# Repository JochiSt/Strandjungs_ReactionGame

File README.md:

# Reaction Game

The idea of this game is that you press a button and after some time (random)
one or two (selectable) wooden rods are dropped. The player has to catch these 
falling rods.

## Modes

There are four different modes implemented. The selection of the modes is done 
via the binary encoded input from the switch (marked with Drop 1/2).
Switch 1 is the LSB and two the MSB.

| Switch 2 	| Switch 1 	| Mode 	| Action                                                                   	|
|----------	|----------	|------	|--------------------------------------------------------------------------	|
| 0        	| 0        	| 0    	| dropping a single random rod                                             	|
| 0        	| 1        	| 1    	| dropping two random rods at the same time                                	|
| 1        	| 0        	| 2    	| dropping two random rods at different times                              	|
| 1        	| 1        	| 3    	| dropping all rods after each other (with waiting time) in a random order 	|

## Operation Voltage & Current
The operation voltage is 12V and the power consumption is about 1.5A (5x200mA for the magnets). 

## Hardware used
* [ElectroMagnets](https://www.amazon.de/gp/product/B07QNL3CJ2)

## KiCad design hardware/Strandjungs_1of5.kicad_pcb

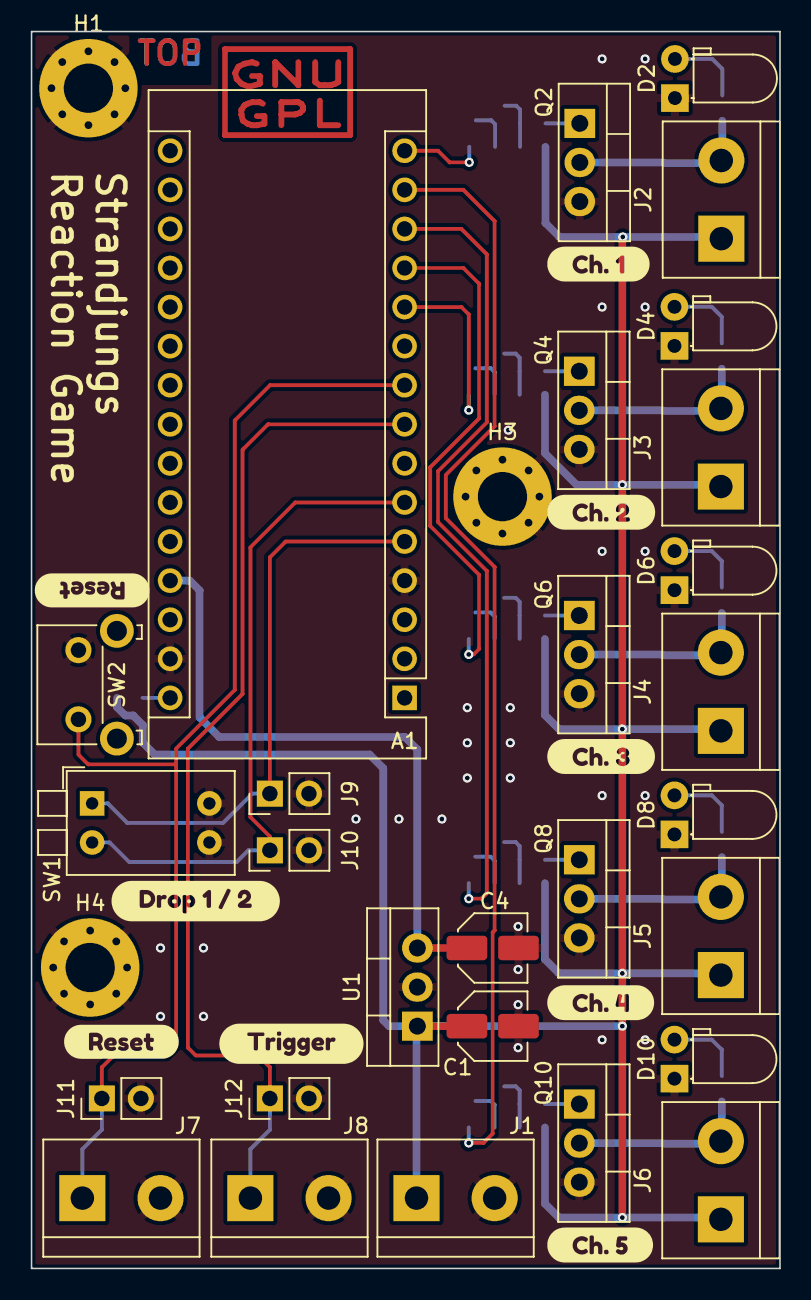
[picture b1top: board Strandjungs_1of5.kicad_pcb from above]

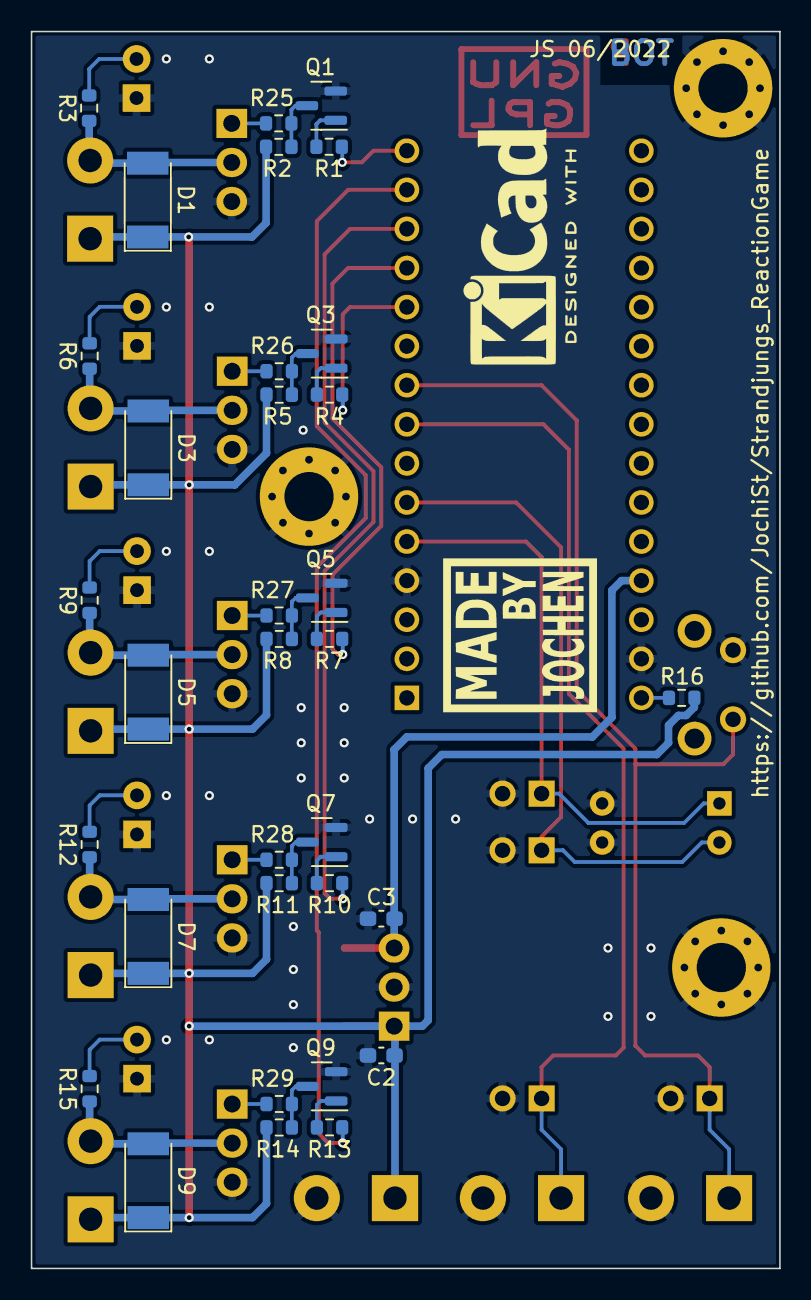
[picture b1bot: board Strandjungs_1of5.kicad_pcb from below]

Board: 2 copper layers, 48.6 x 80.4 mm, 73 parts (33 on the bottom side), 38 nets.

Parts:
A1: Arduino_Nano_v2.x; Arduino_Nano
C1: 1uF; C_Elec_4x5.4
C2, C3: 100n; C_0603_1608Metric_Pad1.08x0.95mm_HandSolder
C4: 10uF; C_Elec_4x5.4
D1, D3, D5, D7, D9: SM4001; D_MELF
D2, D4, D6, D8, D10: LED; LED_D3.0mm_Horizontal_O1.27mm_Z2.0mm
H1, H3, H4: MountingHole_Pad; MountingHole_3.2mm_M3_Pad_Via
J1, J2, J3, J4, J5, J6, J7, J8: Screw_Terminal_01x02; TerminalBlock_bornier-2_P5.08mm
J9, J10, J11, J12: Conn_01x02; PinHeader_1x02_P2.54mm_Vertical
Q1, Q3, Q5, Q7, Q9: BC847; SOT-23
Q2, Q4, Q6, Q8, Q10: BUZ11; TO-220-3_Vertical
R1, R2, R4, R5, R7, R8, R10, R11, R13, R14: 10k; R_0603_1608Metric
R3, R6, R9, R12, R15: 5k6; R_0603_1608Metric
R16: dnp; R_0603_1608Metric
R25, R26, R27, R28, R29: 56; R_0603_1608Metric
SW1: SW_DIP_x02; SW_DIP_SPSTx02_Piano_10.8x6.64mm_W7.62mm_P2.54mm
SW2: SW_Push; SW_Tactile_SKHH_Angled
U1: L7805; TO-220-3_Vertical
kibuzzard-62B9DC86: G***; kibuzzard-62B9DC86
kibuzzard-62B9DCAD, kibuzzard-62B9DCAD#2: G***; kibuzzard-62B9DCAD
kibuzzard-62B9DCC5: G***; kibuzzard-62B9DCC5
kibuzzard-62B9DCD6: G***; kibuzzard-62B9DCD6
kibuzzard-62B9DCE2: G***; kibuzzard-62B9DCE2
kibuzzard-62B9DCF0: G***; kibuzzard-62B9DCF0
kibuzzard-62B9DD05: G***; kibuzzard-62B9DD05
kibuzzard-62B9DD70: G***; kibuzzard-62B9DD70

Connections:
+5V: A1.27 (+5V), C3.1, C4.1, U1.3 (OUT)
+12V: C1.1, C2.1, D1.1 (K), D3.1 (K), D5.1 (K), D7.1 (K), D9.1 (K), J1.1, J2.1, J3.1, J4.1, J5.1, J6.1, R2.1, R5.1, R8.1, R11.1, R14.1, R16.1, U1.1 (IN)
/Channel 0/MAG_RTN: D1.2 (A), J2.2, Q2.2 (D), R3.1
/Channel 1/MAG_RTN: D3.2 (A), J3.2, Q4.2 (D), R6.1
/Channel 2/MAG_RTN: D5.2 (A), J4.2, Q6.2 (D), R9.1
/Channel 3/MAG_RTN: D7.2 (A), J5.2, Q8.2 (D), R12.1
/Channel 4/MAG_RTN: D9.2 (A), J6.2, Q10.2 (D), R15.1
/RESET: A1.9 (D6), J7.1, J11.1, SW2.1
/SEL_0: A1.5 (D2), J9.1, SW1.1
/SEL_1: A1.6 (D3), J10.1, SW1.2
/SWITCH0: A1.15 (D12), R1.1
/SWITCH1: A1.11 (D8), R4.1
/SWITCH2: A1.12 (D9), R7.1
/SWITCH3: A1.13 (D10), R10.1
/SWITCH4: A1.14 (D11), R13.1
/TRIGGER: A1.8 (D5), J8.1, J12.1
GND: A1.4 (GND), A1.29 (GND), C1.2, C2.2, C3.2, C4.2, D2.1 (K), D4.1 (K), D6.1 (K), D8.1 (K), D10.1 (K), H1.1, H3.1, H4.1, J1.2, J7.2, J8.2, J9.2, J10.2, J11.2, J12.2, Q1.2 (E), Q2.3 (S), Q3.2 (E), Q4.3 (S), Q5.2 (E), Q6.3 (S), Q7.2 (E), Q8.3 (S), Q9.2 (E), Q10.3 (S), SW1.3, SW1.4, SW2.2, U1.2 (GND)
unnamed: A1.30 (VIN), R16.2
unnamed: D2.2 (A), R3.2
unnamed: D4.2 (A), R6.2
unnamed: D6.2 (A), R9.2
unnamed: D8.2 (A), R12.2
unnamed: D10.2 (A), R15.2
unnamed: Q1.1 (B), R1.2
unnamed: Q1.3 (C), R2.2, R25.1
unnamed: Q2.1 (G), R25.2
unnamed: Q3.1 (B), R4.2
unnamed: Q3.3 (C), R5.2, R26.1
unnamed: Q4.1 (G), R26.2
unnamed: Q5.1 (B), R7.2
unnamed: Q5.3 (C), R8.2, R27.1
unnamed: Q6.1 (G), R27.2
unnamed: Q7.1 (B), R10.2
unnamed: Q7.3 (C), R11.2, R28.1
unnamed: Q8.1 (G), R28.2
unnamed: Q9.1 (B), R13.2
unnamed: Q9.3 (C), R14.2, R29.1
unnamed: Q10.1 (G), R29.2

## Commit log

2022-06-21 started firmware script
    wrote down the basic ideas and the basic concept.
2022-06-22 added README.md
2022-06-27 added hardware layout
    started layout for driver PCB
2022-06-27 Update .gitignore
    added *.log and *.zip
2022-06-27 first iteration of layout almost done
2022-06-27 added 7805 as voltage regulator
2022-06-28 updated layout
2022-06-28 added description of function
2022-06-28 updated AISLER project ID
2022-06-28 adjusted production output
2022-06-28 added ibom
2022-06-28 ignore PDF
2022-06-29 added pins from schematic
2022-07-03 added rough programming scheme
    some action implemented, needs refinement, once the PCB arrives
2022-07-03 added mode of dropping two rods
2022-07-12 added more modes
2022-07-12 fixed polarity of the system
2022-07-13 fixed random range
2022-07-13 set random seed
    no longer always having the same pattern of dropped rods
2022-07-29 moved waiting into function
    by this the waiting time for all rod dropping actions is always the same (randomized)
2022-07-29 moved button press action to the very beginning
    by this it is no longer required to have one drop in the old mode, when the mode switches are changed.
2022-07-29 added dropping all rods one after each other
2022-07-29 added comments about the different modes
2022-07-29 substituted the waiting time by the function
2022-07-29 some very minor changes regarding configuration and formatting
2022-07-29 fixed dual rod time mode
2022-07-29 added serial output to allow debugging without dropping hardware connected
2022-07-29 added explanation about all the different modes
2022-08-18 added switch position description
2022-11-21 added link to used magnets
2022-11-21 added operation voltage & current estimate
